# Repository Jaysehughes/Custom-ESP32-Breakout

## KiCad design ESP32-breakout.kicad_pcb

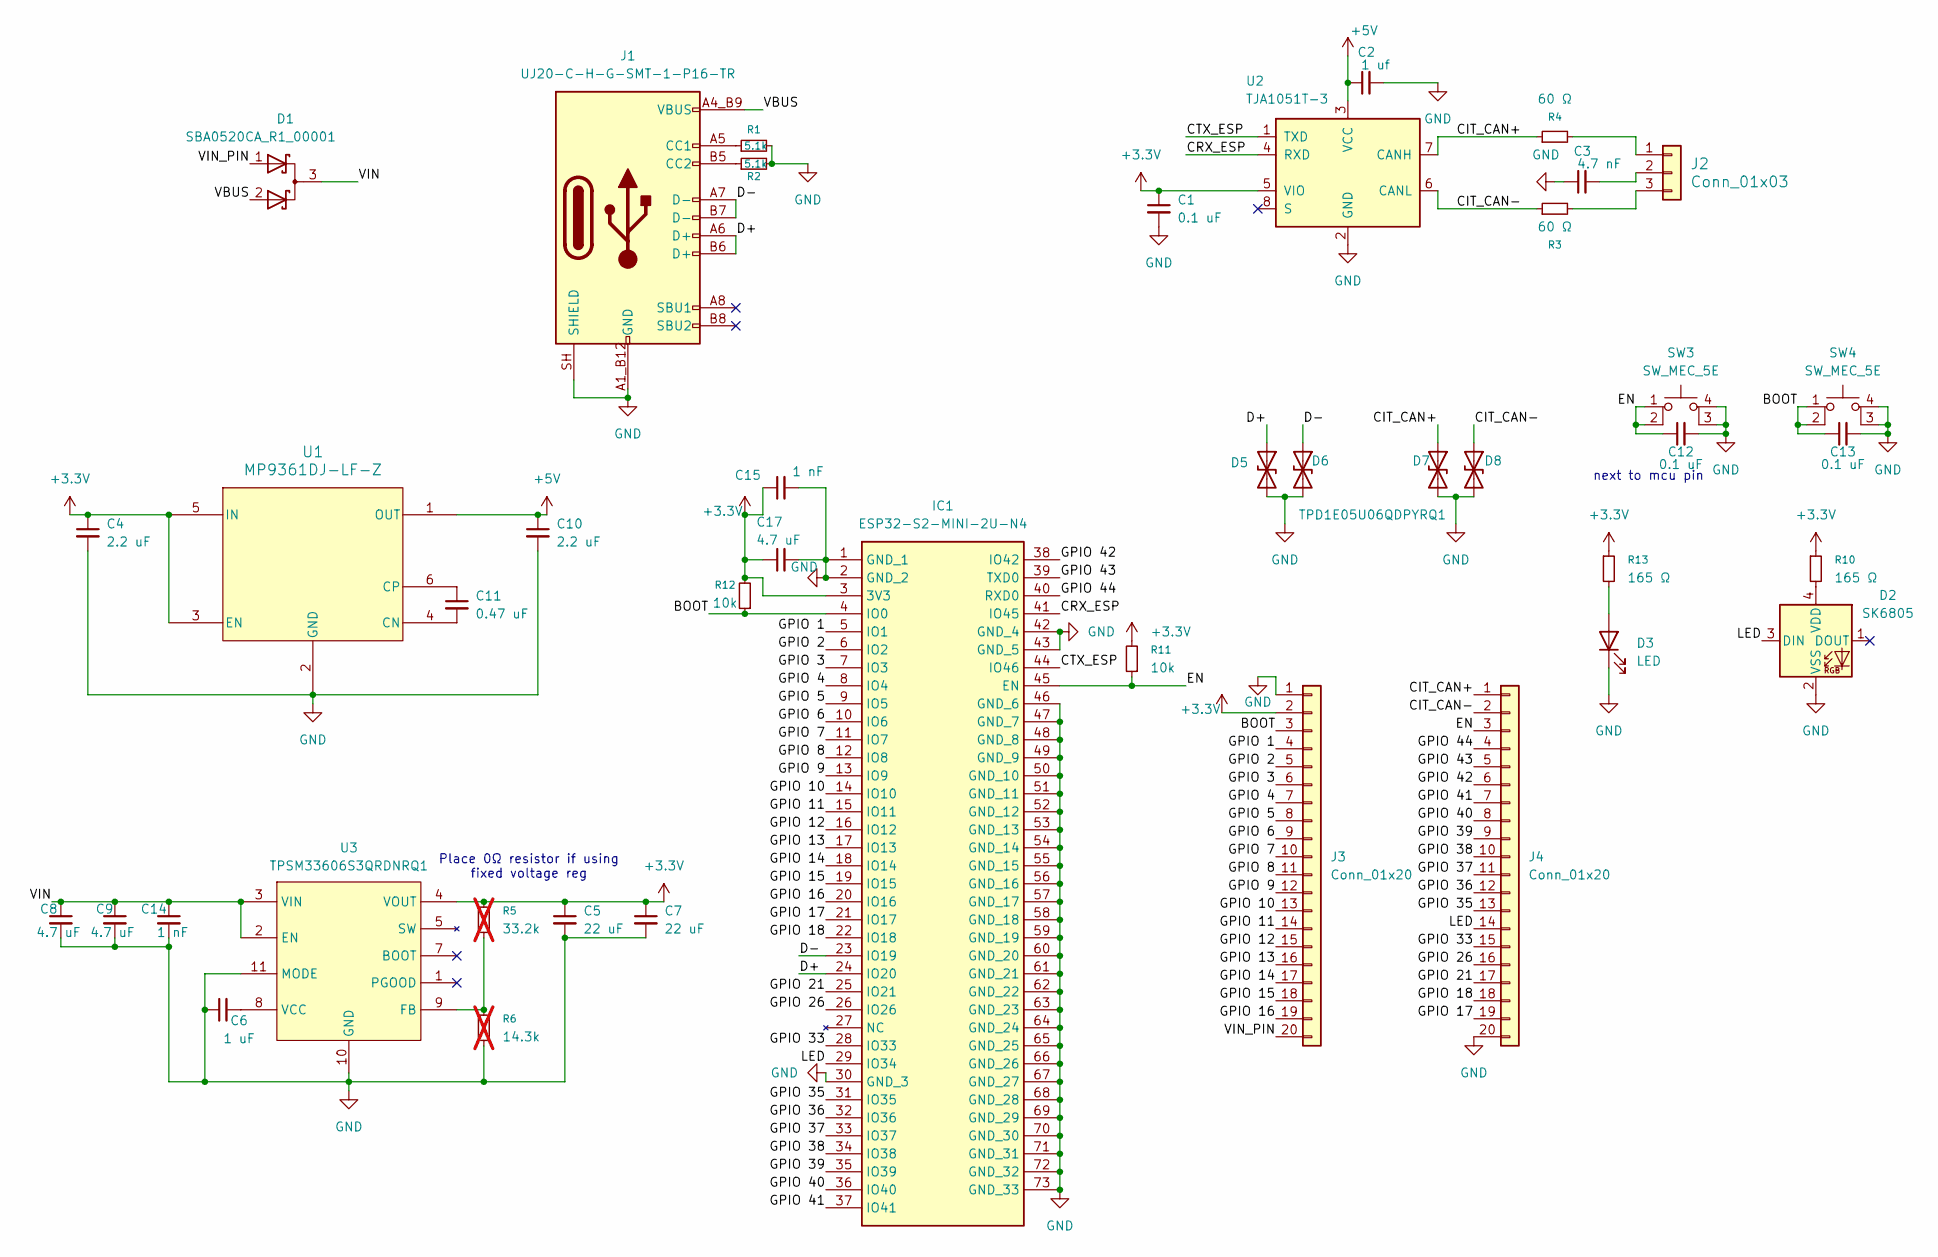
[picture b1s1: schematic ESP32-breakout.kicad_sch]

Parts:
C1, C12, C13: 0.1 uF; C_0402_1005Metric
C2: 1 uf; C_0402_1005Metric
C3: 4.7 nF; C_0402_1005Metric
C4, C10: 2.2 uF; C_0402_1005Metric
C5, C7: 22 uF; C_0402_1005Metric
C6: 1 uF; C_0402_1005Metric
C8, C9: 4.7 uF; C_1206_3216Metric
C11: 0.47 uF; C_0402_1005Metric
C14, C15: 1 nF; C_0402_1005Metric
C17: 4.7 uF; C_0402_1005Metric
D1: SBA0520CA_R1_00001; TSOT-23
D2: SK6805; LED_SK6805_PLCC4_2.4x2.7mm_P1.3mm
D3: LED; LED_0603_1608Metric_Pad1.05x0.95mm_HandSolder
D5, D6, D7, D8: TPD1E05U06QDPYRQ1; D_0603_1608Metric
IC1: ESP32-S2-MINI-2U-N4; ESP32S2MINI2UN4; Manufacturer_Part_Number ESP32-S2-MINI-2U-N4; Mouser Part Number 356-ESP32MINI-2U-N4
J1: UJ20-C-H-G-SMT-1-P16-TR; SAMESKY_UJ20-C-H-G-SMT-1-P16-TR; PARTREV 1.0
J2: Conn_01x03; CONN_S3B-ZR_JST
J3, J4: Conn_01x20; PinHeader_1x20_P2.54mm_Vertical
R1, R2: 5.1k; R_0402_1005Metric
R3, R4: 60 Ω; R_0402_1005Metric
R5: 33.2k; R_0402_1005Metric; not fitted
R6: 14.3k; R_0402_1005Metric; not fitted
R10, R13: 165 Ω; R_0402_1005Metric
R11, R12: 10k; R_0402_1005Metric
SW3, SW4: SW_MEC_5E; NTC013AT1JA160T
U1: MP9361DJ-LF-Z; TSOT23-6_MP9361_MNP
U2: TJA1051T-3; SOIC-8_3.9x4.9mm_P1.27mm
U3: TPSM33606S3QRDNRQ1

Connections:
+3.3V: C1.1, C4.1, C5.1, C7.1, C15.1, C17.1, IC1.3 (3V3), J3.2, R5.1, R10.1, R11.2, R12.2, R13.1, U1.3 (EN), U1.5 (IN), U2.5 (VIO), U3.4 (VOUT)
+5V: C2.1, C10.1, U1.1 (OUT), U2.3 (VCC)
/BOOT: C13.1, IC1.4 (IO0), J3.3, R12.1, SW4.1, SW4.2
/CIT_CAN+: D7.1 (A1), J4.1, R4.1, U2.7 (CANH)
/CIT_CAN-: D8.1 (A1), J4.2, R3.1, U2.6 (CANL)
/CRX_ESP: IC1.41 (IO45), U2.4 (RXD)
/CTX_ESP: IC1.44 (IO46), U2.1 (TXD)
/D+: D5.1 (A1), IC1.24 (IO20), J1.A6 (D+), J1.B6 (D+)
/D-: D6.1 (A1), IC1.23 (IO19), J1.A7 (D-), J1.B7 (D-)
/EN: C12.1, IC1.45 (EN), J4.3, R11.1, SW3.1, SW3.2
/GPIO 1: IC1.5 (IO1), J3.4
/GPIO 2: IC1.6 (IO2), J3.5
/GPIO 3: IC1.7 (IO3), J3.6
/GPIO 4: IC1.8 (IO4), J3.7
/GPIO 5: IC1.9 (IO5), J3.8
/GPIO 6: IC1.10 (IO6), J3.9
/GPIO 7: IC1.11 (IO7), J3.10
/GPIO 8: IC1.12 (IO8), J3.11
/GPIO 9: IC1.13 (IO9), J3.12
/GPIO 10: IC1.14 (IO10), J3.13
/GPIO 11: IC1.15 (IO11), J3.14
/GPIO 12: IC1.16 (IO12), J3.15
/GPIO 13: IC1.17 (IO13), J3.16
/GPIO 14: IC1.18 (IO14), J3.17
/GPIO 15: IC1.19 (IO15), J3.18
/GPIO 16: IC1.20 (IO16), J3.19
/GPIO 17: IC1.21 (IO17), J4.19
/GPIO 18: IC1.22 (IO18), J4.18
/GPIO 21: IC1.25 (IO21), J4.17
/GPIO 26: IC1.26 (IO26), J4.16
/GPIO 33: IC1.28 (IO33), J4.15
/GPIO 35: IC1.31 (IO35), J4.13
/GPIO 36: IC1.32 (IO36), J4.12
/GPIO 37: IC1.33 (IO37), J4.11
/GPIO 38: IC1.34 (IO38), J4.10
/GPIO 39: IC1.35 (IO39), J4.9
/GPIO 40: IC1.36 (IO40), J4.8
/GPIO 41: IC1.37 (IO41), J4.7
/GPIO 42: IC1.38 (IO42), J4.6
/GPIO 43: IC1.39 (TXD0), J4.5
/GPIO 44: IC1.40 (RXD0), J4.4
/LED: D2.3 (DIN), IC1.29 (IO34), J4.14
/VBUS: D1.2 (A), J1.A4_B9 (VBUS), J1.B4_A9 (VBUS)
/VIN: C8.1, C9.1, C14.1, D1.3 (K), U3.2 (EN), U3.3 (VIN)
/VIN_PIN: D1.1 (A), J3.20
GND: C1.2, C2.2, C3.1, C4.2, C5.2, C6.1, C7.2, C8.2, C9.2, C10.2, C12.2, C13.2, C14.2, C15.2, C17.2, D2.2 (VSS), D3.1 (K), D5.2 (A2), D6.2 (A2), D7.2 (A2), D8.2 (A2), IC1.1 (GND_1), IC1.2 (GND_2), IC1.30 (GND_3), IC1.42 (GND_4), IC1.43 (GND_5), IC1.46 (GND_6), IC1.47 (GND_7), IC1.48 (GND_8), IC1.49 (GND_9), IC1.50 (GND_10), IC1.51 (GND_11), IC1.52 (GND_12), IC1.53 (GND_13), IC1.54 (GND_14), IC1.55 (GND_15), IC1.56 (GND_16), IC1.57 (GND_17), IC1.58 (GND_18), IC1.59 (GND_19), IC1.60 (GND_20), IC1.61 (GND_21), IC1.62 (GND_22), IC1.63 (GND_23), IC1.64 (GND_24), IC1.65 (GND_25), IC1.66 (GND_26), IC1.67 (GND_27), IC1.68 (GND_28), IC1.69 (GND_29), IC1.70 (GND_30), IC1.71 (GND_31), IC1.72 (GND_32), IC1.73 (GND_33), J1.A1_B12 (GND), J1.B1_A12 (GND), J1.SH (SHIELD), J1.SH2, J1.SH3, J1.SH4, J3.1, J4.20, R1.2, R2.2, R6.2, SW3.3 (K), SW3.4 (A), SW4.3 (K), SW4.4 (A), U1.2 (GND), U2.2 (GND), U3.10 (GND), U3.11 (MODE)
unnamed: D2.4 (VDD), R10.2
unnamed: D3.2 (A), R13.2
unnamed: J1.A5 (CC1), R1.1
unnamed: J1.B5 (CC2), R2.1
unnamed: J2.1, R4.2
unnamed: C3.2, J2.2
unnamed: J2.3, R3.2
unnamed: C11.2, U1.4 (CN)
unnamed: C11.1, U1.6 (CP)
unnamed: R5.2, R6.1, U3.9 (FB)
unnamed: C6.2, U3.8 (VCC)

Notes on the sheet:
Place 0Ω resistor if using fixed voltage reg
next to mcu pin

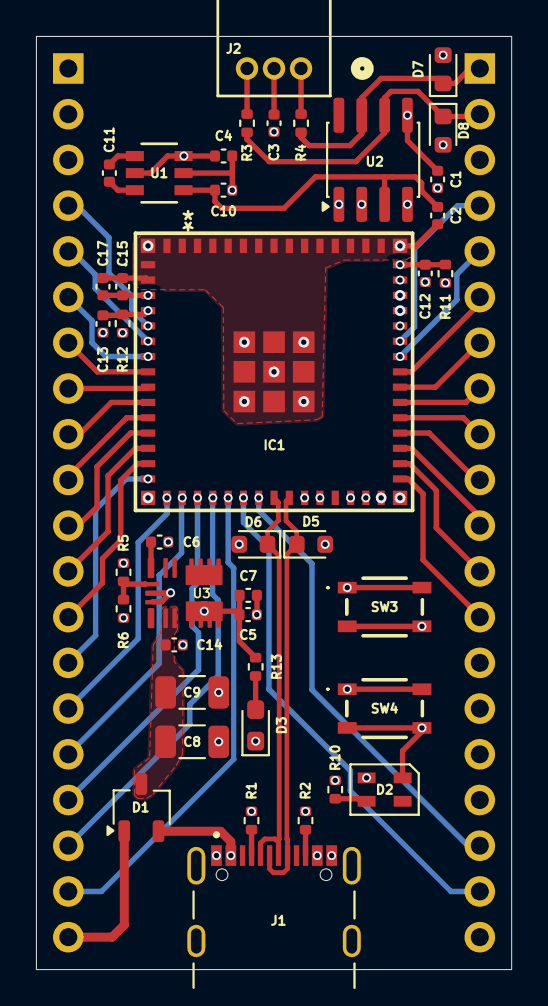
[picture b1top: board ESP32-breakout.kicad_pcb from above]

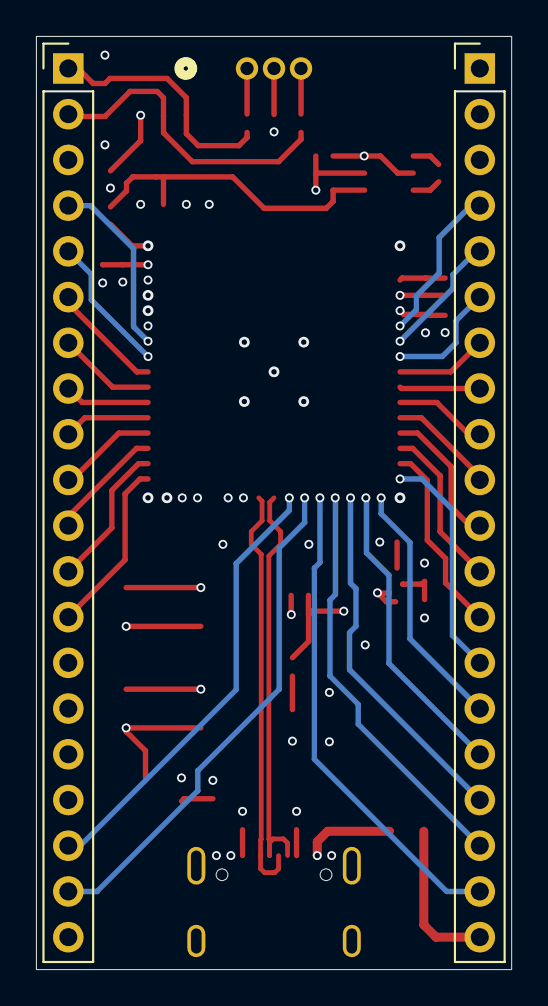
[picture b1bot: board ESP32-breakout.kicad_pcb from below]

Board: 6 copper layers, 26.4 x 51.8 mm, 43 parts (2 on the bottom side), 57 nets.

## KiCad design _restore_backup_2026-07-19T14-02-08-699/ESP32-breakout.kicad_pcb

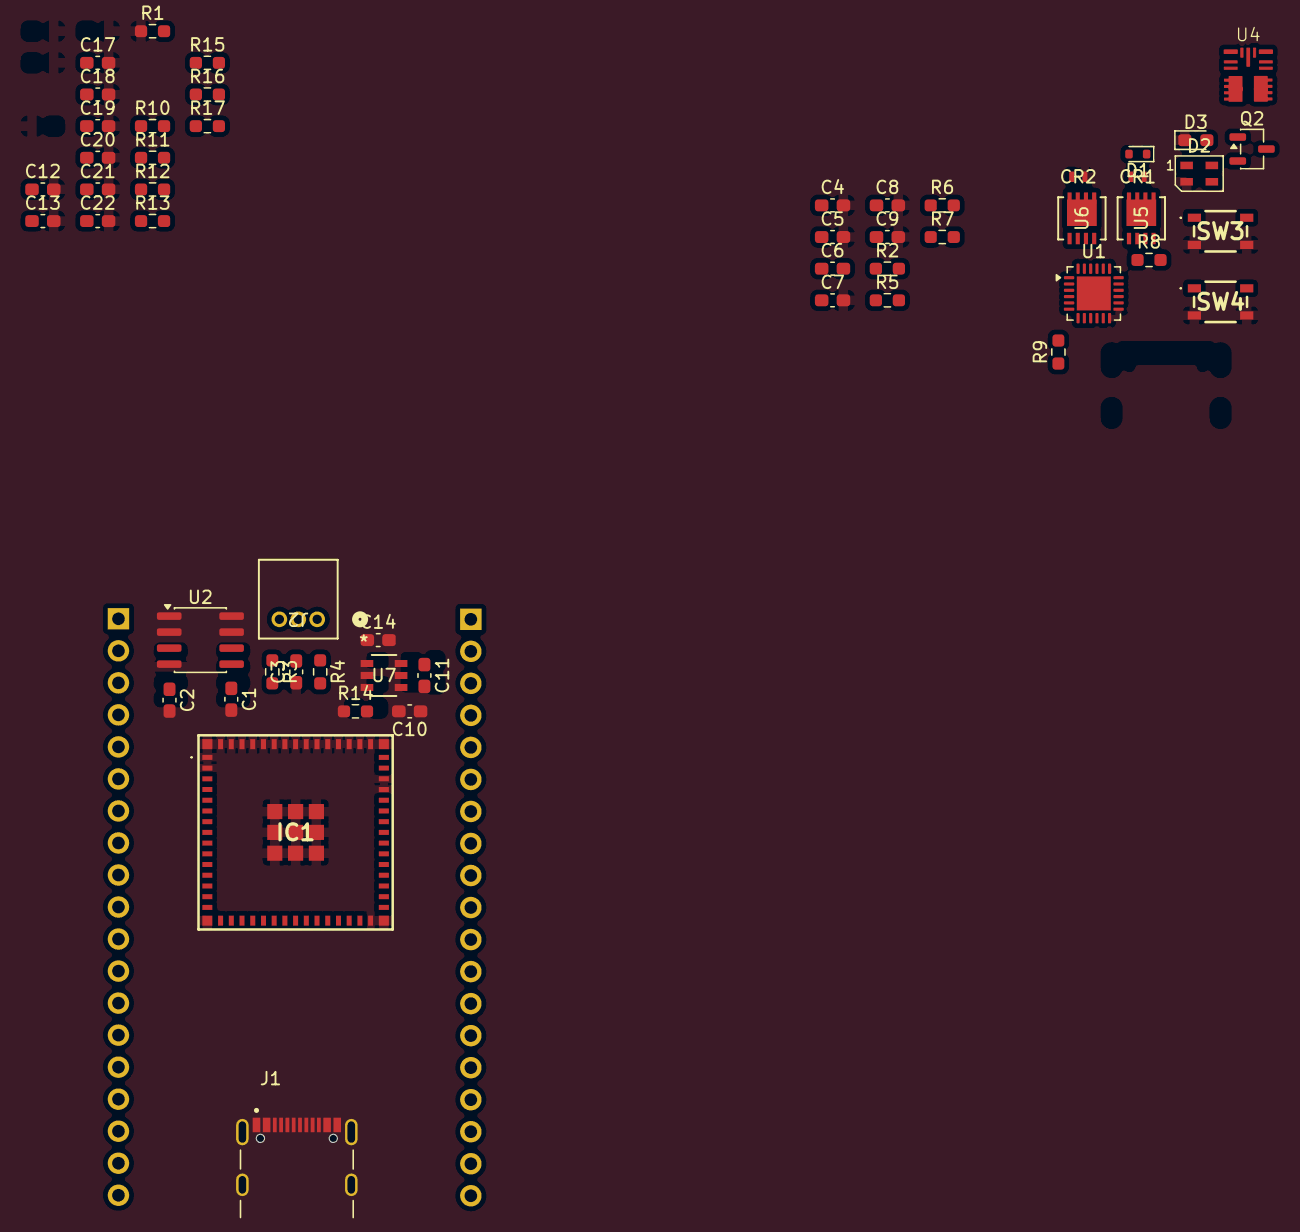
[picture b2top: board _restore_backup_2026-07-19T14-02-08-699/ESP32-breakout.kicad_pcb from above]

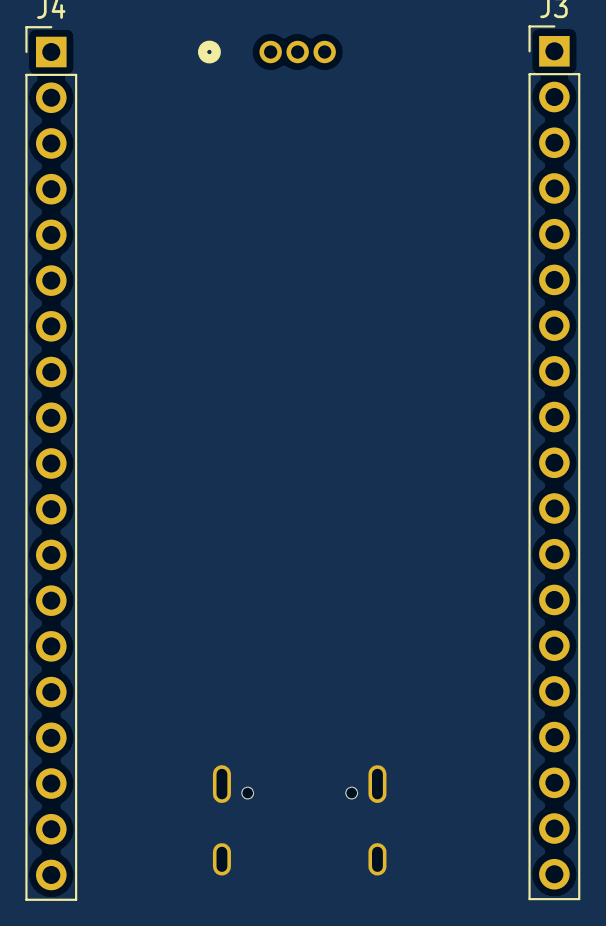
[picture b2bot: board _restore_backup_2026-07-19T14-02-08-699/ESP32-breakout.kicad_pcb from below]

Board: 2 copper layers, 56 parts (2 on the bottom side), 39 nets, no tracks yet.

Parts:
C1, C12, C13, C19: 0.1 uF; C_0603_1608Metric_Pad1.08x0.95mm_HandSolder
C2: 1 uf; C_0603_1608Metric_Pad1.08x0.95mm_HandSolder
C3: 4.7 nF; C_0603_1608Metric_Pad1.08x0.95mm_HandSolder
C4: 4.7uF; C_0603_1608Metric_Pad1.08x0.95mm_HandSolder
C5, C7, C8, C9: 1uF; C_0603_1608Metric_Pad1.08x0.95mm_HandSolder
C6: 100nF; C_0603_1608Metric_Pad1.08x0.95mm_HandSolder
C10, C14: 2.2 uF; C_0603_1608Metric_Pad1.08x0.95mm_HandSolder
C11: 0.47 uF; C_0603_1608Metric_Pad1.08x0.95mm_HandSolder
C17, C18: 4.7 uF; C_0603_1608Metric_Pad1.08x0.95mm_HandSolder
C20: 1 uF; C_0603_1608Metric_Pad1.08x0.95mm_HandSolder
C21, C22: 22 uF; C_0603_1608Metric_Pad1.08x0.95mm_HandSolder
CR1, CR2: ESDA25P35-1U1M; QFN1610_STM
D1: 1N4148WT; D_SOD-523
D2: SK6805; LED_SK6805_PLCC4_2.4x2.7mm_P1.3mm
D3: LED; LED_0603_1608Metric_Pad1.05x0.95mm_HandSolder
IC1: ESP32-S2-MINI-2U-N4; ESP32S2MINI2UN4
J1: UJ20-C-H-G-SMT-1-P16-TR; SAMESKY_UJ20-C-H-G-SMT-1-P16-TR
J2: Conn_01x03; CONN_S3B-ZR_JST
J3, J4: Conn_01x19; PinHeader_1x19_P2.54mm_Vertical
Q2: Q_NMOS_DGS; SOT-23-3
R1, R11, R12, R14: 10k; R_0603_1608Metric_Pad0.98x0.95mm_HandSolder
R2: 470; R_0603_1608Metric_Pad0.98x0.95mm_HandSolder
R3, R4: 60 Ω; R_0603_1608Metric_Pad0.98x0.95mm_HandSolder
R5, R9: 1k; R_0603_1608Metric_Pad0.98x0.95mm_HandSolder
R6: 22k; R_0603_1608Metric_Pad0.98x0.95mm_HandSolder
R7, R15: 100k; R_0603_1608Metric_Pad0.98x0.95mm_HandSolder
R8: 100; R_0603_1608Metric_Pad0.98x0.95mm_HandSolder
R10, R13: 165; R_0603_1608Metric_Pad0.98x0.95mm_HandSolder
R16, R17: 4.7; R_0603_1608Metric_Pad0.98x0.95mm_HandSolder
SW3, SW4: SW_MEC_5E; NTC013AT1JA160T
U1: STUSB4500QTR; QFN-24-1EP_4x4mm_P0.5mm_EP2.7x2.7mm
U2: TJA1051T-3; SOIC-8_3.9x4.9mm_P1.27mm
U4: TPSM33606S3QRDNRQ1
U5, U6: STL6P3LLH6; POWERFLAT_3P3X3P3_STM
U7: MP9361DJ-LF-Z; TSOT23-6_MP9361_MNP

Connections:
+3.3V: C1.1, C10.2, C17.1, C21.1, C22.1, IC1.3 (3V3), R10.1, R11.2, R12.2, R13.1, R14.1, R16.1, R17.1, U2.5 (VIO), U4.4 (VOUT), U4.9 (FB), U7.5 (IN)
+5VCAN: C2.1, C14.1, U2.3 (VCC), U7.1 (OUT)
/Attach: Q2.2 (G), R15.2, U1.11 (ATTACH)
/BOOT: C13.1, IC1.4 (IO0), R12.1, SW4.1, SW4.2
/CC1: J1.A5 (CC1), U1.1 (CC1DB), U1.2 (CC1)
/CC2: J1.B5 (CC2), U1.4 (CC2), U1.5 (CC2DB)
/CIT_CAN+: R3.2, U2.7 (CANH)
/CIT_CAN-: R4.2, U2.6 (CANL)
/CRX_ESP: IC1.9 (IO5), U2.4 (RXD)
/CTX_ESP: IC1.8 (IO4), U2.1 (TXD)
/D+: IC1.24 (IO20), J1.A6 (D+), J1.B6 (D+)
/D-: IC1.23 (IO19), J1.A7 (D-), J1.B7 (D-)
/EN: C12.1, IC1.45 (EN), R11.1, SW3.1, SW3.2
/LED: D2.3 (DIN), IC1.10 (IO6)
/RESET_USB: R1.2, U1.6 (RESET)
/SCL: IC1.11 (IO7), R16.2, U1.7 (SCL)
/SDA: IC1.12 (IO8), R17.2, U1.8 (SDA)
/Vin: Q2.1 (D), R15.1
DISCH: R9.1, U1.9 (DISCH)
GND: C1.2, C2.2, C3.1, C4.2, C5.2, C7.2, C8.2, C9.2, C10.1, C12.2, C13.2, C14.2, C17.2, C18.2, C19.2, C20.2, C21.2, C22.2, CR1.2, CR2.2, D2.2 (VSS), D3.1 (K), IC1.1 (GND_1), IC1.2 (GND_2), IC1.30 (GND_3), IC1.42 (GND_4), IC1.43 (GND_5), IC1.46 (GND_6), IC1.47 (GND_7), IC1.48 (GND_8), IC1.49 (GND_9), IC1.50 (GND_10), IC1.51 (GND_11), IC1.52 (GND_12), IC1.53 (GND_13), IC1.54 (GND_14), IC1.55 (GND_15), IC1.56 (GND_16), IC1.57 (GND_17), IC1.58 (GND_18), IC1.59 (GND_19), IC1.60 (GND_20), IC1.61 (GND_21), IC1.62 (GND_22), IC1.63 (GND_23), IC1.64 (GND_24), IC1.65 (GND_25), IC1.66 (GND_26), IC1.67 (GND_27), IC1.68 (GND_28), IC1.69 (GND_29), IC1.70 (GND_30), IC1.71 (GND_31), IC1.72 (GND_32), IC1.73 (GND_33), R1.1, SW3.3 (K), SW3.4 (A), SW4.3 (K), SW4.4 (A), U1.10 (GND), U1.12 (ADDR0), U1.13 (ADDR1), U1.22 (VSYS), U1.25 (GND), U2.2 (GND), U4.10 (GND), U4.11 (MODE), U7.2 (GND)
unnamed: C6.2, R8.2
unnamed: C5.1, D1.1 (K), R2.2, R5.1
unnamed: D2.4 (VDD), R10.2
unnamed: D3.2 (A), R13.2
unnamed: J2.1, R4.1
unnamed: C3.2, J2.2
unnamed: J2.3, R3.1
unnamed: C20.1, U4.8 (VCC)
unnamed: R6.1, R7.1, R8.1, U5.4 (G), U6.4 (G)
unnamed: C11.2, U7.4 (CN)
unnamed: C11.1, U7.6 (CP)
unnamed: R14.2, U7.3 (EN)
VBUS: C4.1, CR1.1, D1.2 (A), R2.1, U5.5 (D), U5.6 (D), U5.7 (D), U5.8 (D)
VBUS_EN_SNK: R6.2, U1.16 (VBUS_EN_SNK)
VBUS_VS_DISCH: R5.2, U1.18 (VBUS_VS_DISCH)
VDD_USB: C7.1, R7.2, U1.24 (VDD), U5.1 (S), U5.2 (S), U5.3 (S), U6.1 (S), U6.2 (S), U6.3 (S)
VREG_1V2: C8.1, U1.21 (VREG_1V2)
VREG_2V7: C9.1, U1.23 (VREG_2V7)
VSINK: C6.1, C18.1, C19.1, CR2.1, Q2.3 (S), R9.2, U4.2 (EN), U4.3 (VIN), U6.5 (D), U6.6 (D), U6.7 (D), U6.8 (D)

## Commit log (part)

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2026-06-30 Inital Commit
